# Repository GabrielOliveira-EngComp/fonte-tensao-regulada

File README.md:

# ⚡ Fonte Regulada Super Choke

Projeto de uma fonte de tensão regulada com saídas fixas e ajustáveis, utilizando os reguladores **LM7805** e **LM317**. Desenvolvido com esquemático, layout de PCI e visualização 3D no KiCad, além da montagem real da placa.

---

## 🔧 Componentes Principais

- LM7805 – Tensão fixa +5V
- LM317 – Tensão ajustável (1.25V até 12V)
- Diodos 1N5408 (retificação)
- Capacitores eletrolíticos (2200µF, 1000µF, 470µF)
- LED indicador
- Dissipadores de calor
- Conectores de entrada e saída (borne parafuso)

---

## 🛠️ Recursos do Projeto

- Entrada AC via transformador (conector de três pinos)
- Retificação com diodos de potência
- Regulagem linear com dissipação térmica
- Saída dupla:
  - 🔹 +5V fixa com LM7805
  - 🔹 +VREG ajustável com LM317
- Proteção com diodos de retorno e capacitores de filtragem
- LED indicador de funcionamento

---

## 🧠 Tecnologias Utilizadas

- **KiCad** para esquemático, layout e visualização 3D
- Projeto de trilhas e footprint manual
- Simulação elétrica básica e revisão de malha GND
- Projeto pronto para produção da PCI

---

## 📐 Esquemático

---

## 🔵 Layout da Placa (PCI)

---

## 🟢 Visualização 3D

---

## 📸 Placa Real Montada

Foto da versão física da fonte regulada montada e testada com sucesso:

> *Projeto 100% funcional, ideal para bancadas e testes com sistemas embarcados.*

---

## ⚙️ Aplicações

- Fontes de bancada para testes
- Projetos com microcontroladores (ESP32, Arduino, etc.)
- Prototipagem eletrônica
- Aplicações educacionais

---

## 👨‍💻 Autor

**Gabriel Barbosa Fernandes de Oliveira**  
Estudante de Engenharia de Computação – PUCPR  
🔗 [LinkedIn](https://www.linkedin.com/in/gabrielengcomp/)

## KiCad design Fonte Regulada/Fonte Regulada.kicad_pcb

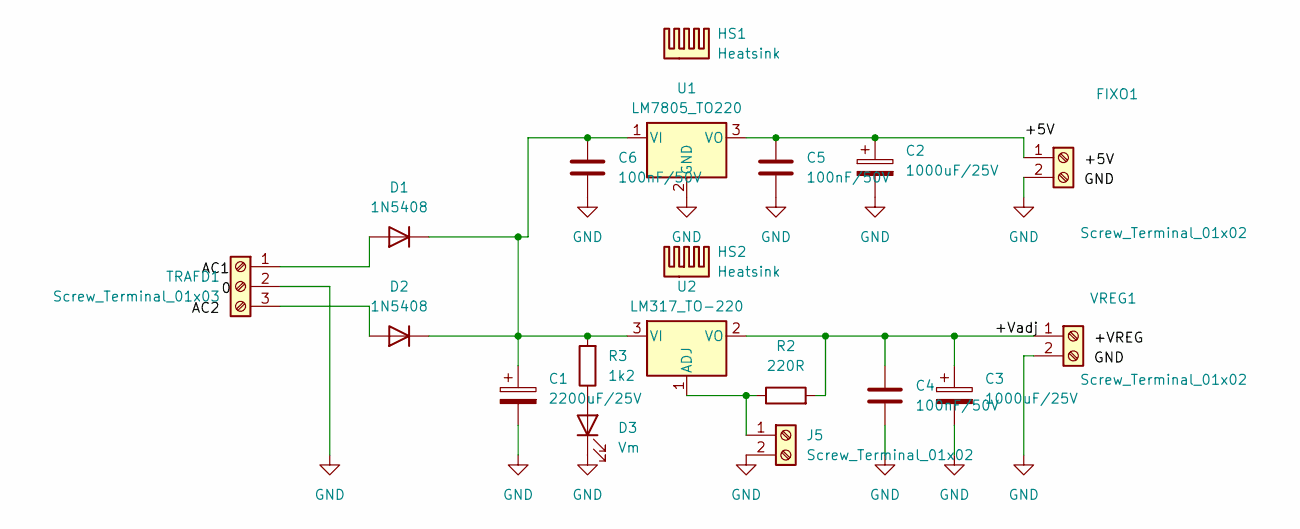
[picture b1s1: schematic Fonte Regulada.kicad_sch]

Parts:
C1: 2200uF/25V; CP_Radial_D17.0mm_P7.50mm
C2, C3: 1000uF/25V; CP_Radial_D10.0mm_P5.00mm
C4, C5, C6: 100nF/50V; C_Disc_D5.1mm_W3.2mm_P5.00mm
D1, D2: 1N5408; D_DO-201AD_P15.24mm_Horizontal
D3: Vm; LED_D5.0mm
FIXO1: Screw_Terminal_01x02; TerminalBlock_Phoenix_MKDS-1,5-2-5.08_1x02_P5.08mm_Horizont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
HS1, HS2: Heatsink; Heatsink_35x26mm_1xFixation3mm_Fischer-SK486-35
J5: Screw_Terminal_01x02; TerminalBlock_Phoenix_MKDS-1,5-2-5.08_1x02_P5.08mm_Horizont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
R2: 220R; R_Axial_DIN0207_L6.3mm_D2.5mm_P10.16mm_Horizontal
R3: 1k2; R_Axial_DIN0207_L6.3mm_D2.5mm_P10.16mm_Horizontal
TRAFD1: Screw_Terminal_01x03; TerminalBlock_Phoenix_MKDS-1,5-3-5.08_1x03_P5.08mm_Horizont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
U1: LM7805_TO220; TO-220-3_Horizontal_TabDown
U2: LM317_TO-220; TO-220-3_Horizontal_TabDown
VREG1: Screw_Terminal_01x02; TerminalBlock_Phoenix_MKDS-1,5-2-5.08_1x02_P5.08mm_Horizont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

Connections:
/+5V: C2.1, C5.1, FIXO1.1, U1.3 (VO)
/+Vadj: C3.1, C4.1, R2.2, U2.2 (VO), VREG1.1
GND: C1.2, C2.2, C3.2, C4.2, C5.2, C6.2, D3.1 (K), FIXO1.2, J5.2, TRAFD1.2, U1.2 (GND), VREG1.2
unnamed: D1.2 (A), TRAFD1.1
unnamed: C1.1, C6.1, D1.1 (K), D2.1 (K), R3.2, U1.1 (VI), U2.3 (VI)
unnamed: D2.2 (A), TRAFD1.3
unnamed: D3.2 (A), R3.1
unnamed: J5.1, R2.1, U2.1 (ADJ)

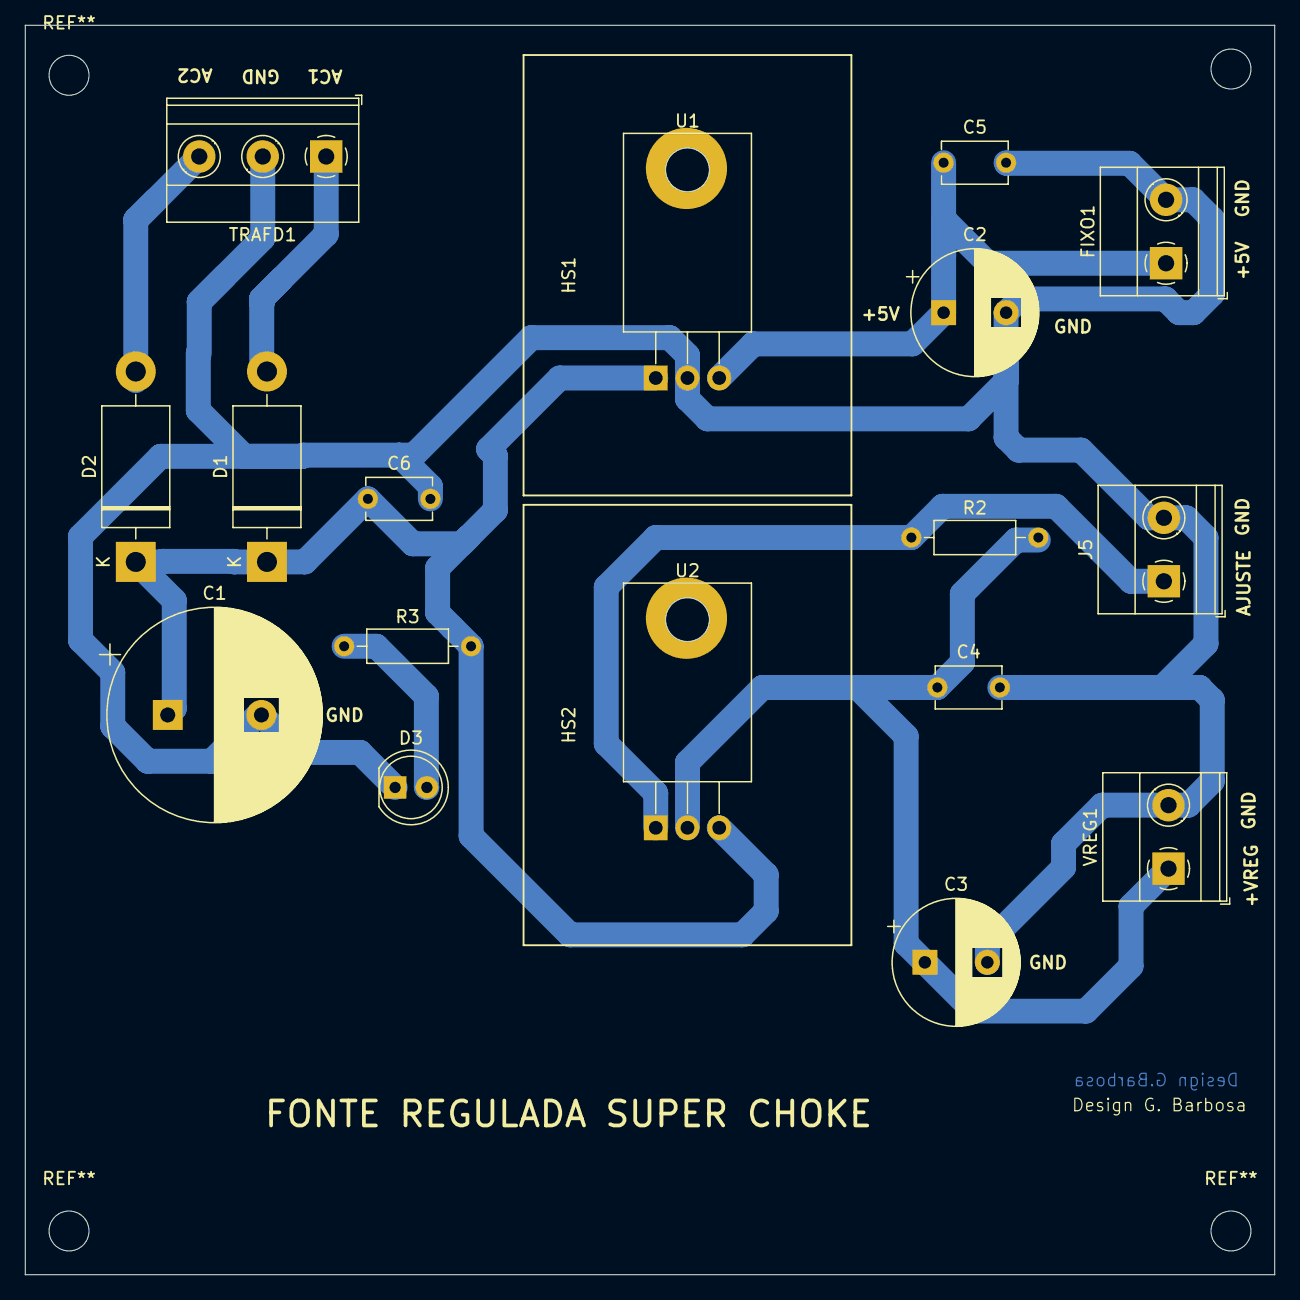
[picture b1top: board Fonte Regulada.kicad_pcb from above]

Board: 2 copper layers, 100.0 x 100.0 mm, 19 parts (0 on the bottom side), 8 nets.
